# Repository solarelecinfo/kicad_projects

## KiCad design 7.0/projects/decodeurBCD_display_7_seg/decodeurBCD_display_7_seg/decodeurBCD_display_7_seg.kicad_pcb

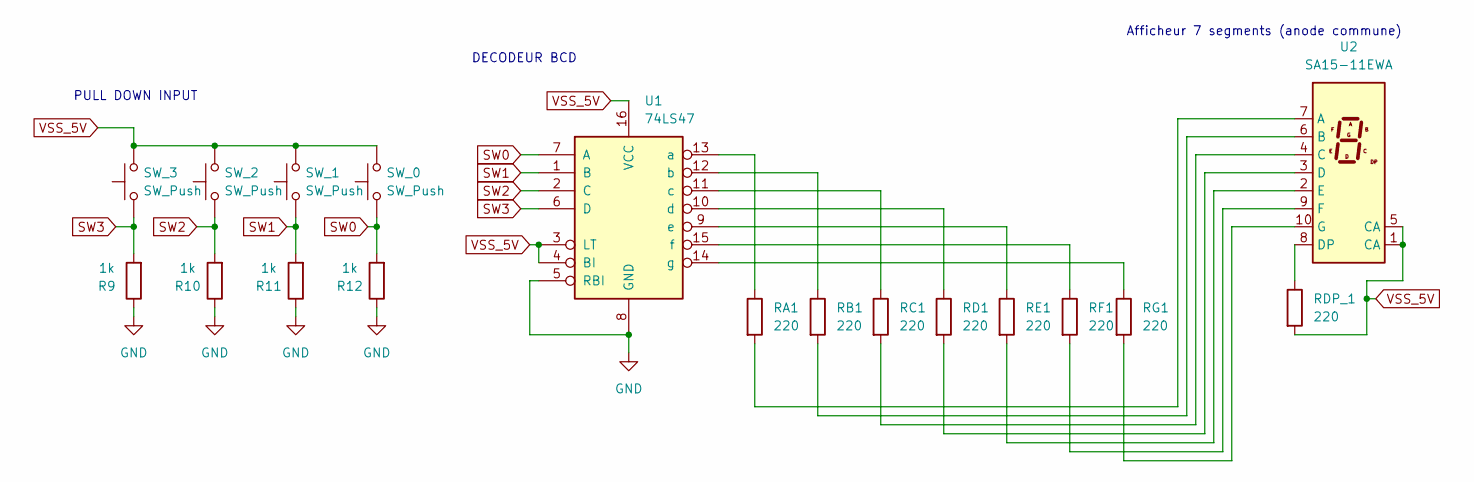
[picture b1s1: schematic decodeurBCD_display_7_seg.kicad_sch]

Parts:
R9, R10, R11, R12: 1k; R_Axial_DIN0411_L9.9mm_D3.6mm_P7.62mm_Vertical
RA1: 220; R_Axial_DIN0411_L9.9mm_D3.6mm_P7.62mm_Vertical
RB1: 220; R_Axial_DIN0411_L9.9mm_D3.6mm_P7.62mm_Vertical
RC1: 220; R_Axial_DIN0411_L9.9mm_D3.6mm_P7.62mm_Vertical
RD1: 220; R_Axial_DIN0411_L9.9mm_D3.6mm_P7.62mm_Vertical
RDP_1: 220; R_Axial_DIN0411_L9.9mm_D3.6mm_P7.62mm_Vertical
RE1: 220; R_Axial_DIN0411_L9.9mm_D3.6mm_P7.62mm_Vertical
RF1: 220; R_Axial_DIN0411_L9.9mm_D3.6mm_P7.62mm_Vertical
RG1: 220; R_Axial_DIN0411_L9.9mm_D3.6mm_P7.62mm_Vertical
SW_0, SW_1, SW_2, SW_3: SW_Push; SW_PUSH_6mm_H5mm
U1: 74LS47; CERDIP-16_W7.62mm_SideBrazed_Socket
U2: SA15-11EWA; SA15-11xxx

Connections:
GND: R9.1, R10.1, R11.1, R12.1, U1.5 (RBI), U1.8 (GND)
unnamed: RA1.1, U1.13 (a)
unnamed: RB1.1, U1.12 (b)
unnamed: RC1.1, U1.11 (c)
unnamed: RD1.1, U1.10 (d)
unnamed: RE1.1, U1.9 (e)
unnamed: RF1.1, U1.15 (f)
unnamed: RG1.1, U1.14 (g)
unnamed: RA1.2, U2.7 (A)
unnamed: RB1.2, U2.6 (B)
unnamed: RC1.2, U2.4 (C)
unnamed: RD1.2, U2.3 (D)
unnamed: RDP_1.1, U2.8 (DP)
unnamed: RE1.2, U2.2 (E)
unnamed: RF1.2, U2.9 (F)
unnamed: RG1.2, U2.10 (G)
SW0: R12.2, SW_0.1, U1.7 (A)
SW1: R11.2, SW_1.1, U1.1 (B)
SW2: R10.2, SW_2.1, U1.2 (C)
SW3: R9.2, SW_3.1, U1.6 (D)
VSS_5V: RDP_1.2, SW_0.2, SW_1.2, SW_2.2, SW_3.2, U1.3 (LT), U1.4 (BI), U1.16 (VCC), U2.1 (CA), U2.5 (CA)

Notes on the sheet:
PULL DOWN INPUT
DECODEUR BCD
Afficheur 7 segments (anode commune)

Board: 2 copper layers, 18 parts (0 on the bottom side), 21 nets, no tracks yet.

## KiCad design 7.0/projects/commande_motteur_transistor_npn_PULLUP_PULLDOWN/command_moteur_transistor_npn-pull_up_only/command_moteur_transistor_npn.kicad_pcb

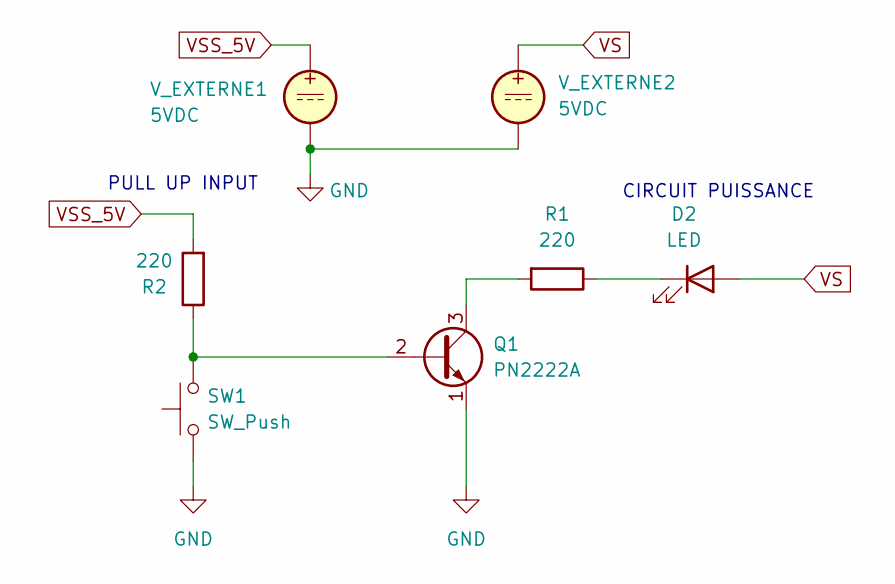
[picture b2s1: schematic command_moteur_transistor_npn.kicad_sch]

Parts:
D2: LED; LED_D5.0mm
Q1: PN2222A; TO-92_Inline
R1, R2: 220; R_Axial_DIN0411_L9.9mm_D3.6mm_P7.62mm_Vertical
SW1: SW_Push; PinSocket_1x02_P2.54mm_Vertical
V_EXTERNE1, V_EXTERNE2: 5VDC; PinHeader_1x02_P2.54mm_Horizontal

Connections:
GND: Q1.1 (E), SW1.1, V_EXTERNE1.2, V_EXTERNE2.2
unnamed: D2.1 (K), R1.1
unnamed: Q1.2 (B), R2.1, SW1.2
unnamed: Q1.3 (C), R1.2
VS: D2.2 (A), V_EXTERNE2.1
VSS_5V: R2.2, V_EXTERNE1.1

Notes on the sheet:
PULL UP INPUT
CIRCUIT PUISSANCE

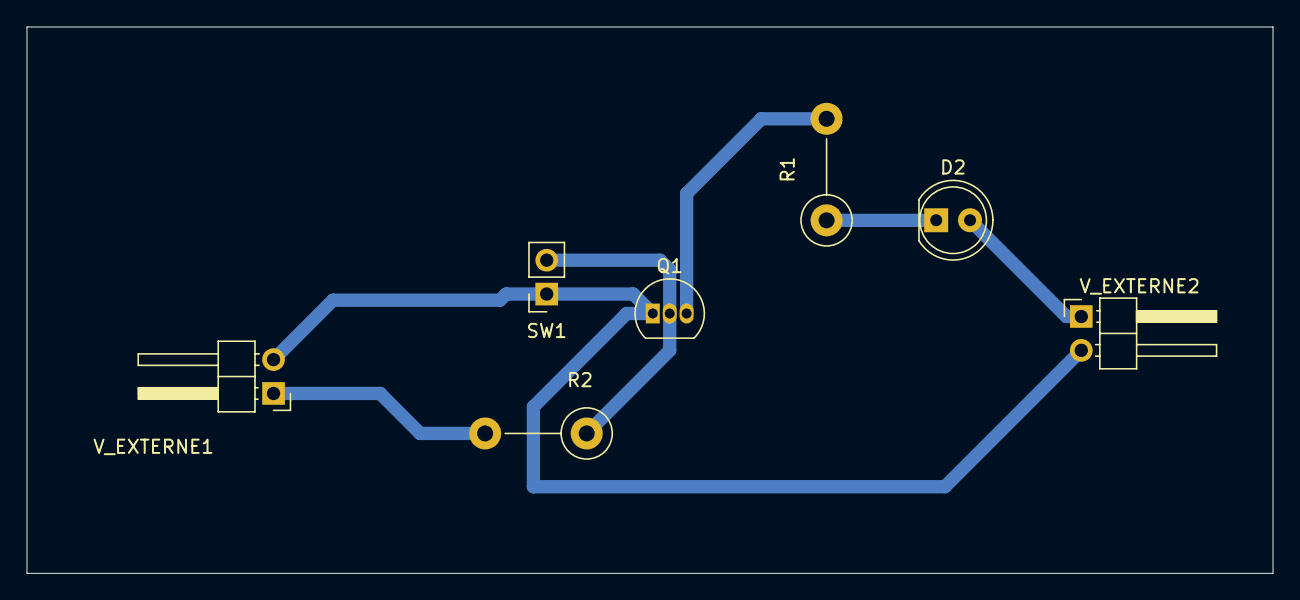
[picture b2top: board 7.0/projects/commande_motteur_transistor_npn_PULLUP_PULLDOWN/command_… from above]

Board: 2 copper layers, 93.5 x 41.0 mm, 7 parts (0 on the bottom side), 6 nets.

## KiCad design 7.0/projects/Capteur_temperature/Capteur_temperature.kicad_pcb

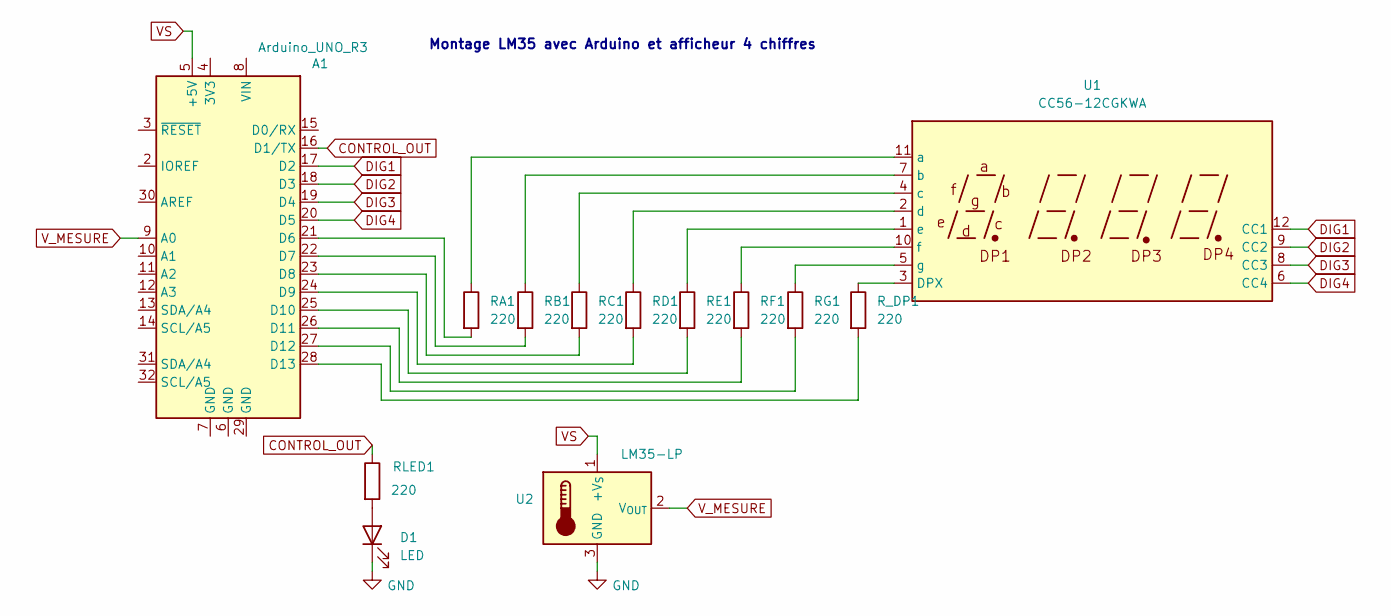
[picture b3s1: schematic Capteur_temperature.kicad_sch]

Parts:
A1: Arduino_UNO_R3
D1: LED; LED_D5.0mm
RA1: 220; R_Axial_DIN0411_L9.9mm_D3.6mm_P12.70mm_Horizontal
RB1: 220; R_Axial_DIN0411_L9.9mm_D3.6mm_P12.70mm_Horizontal
RC1: 220; R_Axial_DIN0411_L9.9mm_D3.6mm_P12.70mm_Horizontal
RD1: 220; R_Axial_DIN0411_L9.9mm_D3.6mm_P12.70mm_Horizontal
RE1: 220; R_Axial_DIN0411_L9.9mm_D3.6mm_P12.70mm_Horizontal
RF1: 220; R_Axial_DIN0411_L9.9mm_D3.6mm_P12.70mm_Horizontal
RG1: 220; R_Axial_DIN0411_L9.9mm_D3.6mm_P12.70mm_Horizontal
RLED1: 220; R_Axial_DIN0411_L9.9mm_D3.6mm_P12.70mm_Horizontal
R_DP1: 220; R_Axial_DIN0411_L9.9mm_D3.6mm_P12.70mm_Horizontal
U1: CC56-12CGKWA; CA56-12CGKWA
U2: LM35-LP; TO-92_Inline

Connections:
CONTROL_OUT: A1.16 (D1/TX), RLED1.1
DIG1: A1.17 (D2), U1.12 (CC1)
DIG2: A1.18 (D3), U1.9 (CC2)
DIG3: A1.19 (D4), U1.8 (CC3)
DIG4: A1.20 (D5), U1.6 (CC4)
GND: D1.1 (K), U2.3 (GND)
unnamed: A1.21 (D6), RA1.2
unnamed: A1.22 (D7), RB1.2
unnamed: A1.23 (D8), RC1.2
unnamed: A1.24 (D9), RD1.2
unnamed: A1.25 (D10), RE1.2
unnamed: A1.26 (D11), RF1.2
unnamed: A1.27 (D12), RG1.2
unnamed: A1.28 (D13), R_DP1.2
unnamed: D1.2 (A), RLED1.2
unnamed: R_DP1.1, U1.3 (DPX)
unnamed: RA1.1, U1.11 (a)
unnamed: RB1.1, U1.7 (b)
unnamed: RC1.1, U1.4 (c)
unnamed: RD1.1, U1.2 (d)
unnamed: RE1.1, U1.1 (e)
unnamed: RF1.1, U1.10 (f)
unnamed: RG1.1, U1.5 (g)
VS: A1.5 (+5V), U2.1 (+V_{S})
V_MESURE: A1.9 (A0), U2.2 (V_{OUT})

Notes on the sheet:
Montage LM35 avec Arduino et afficheur 4 chiffres

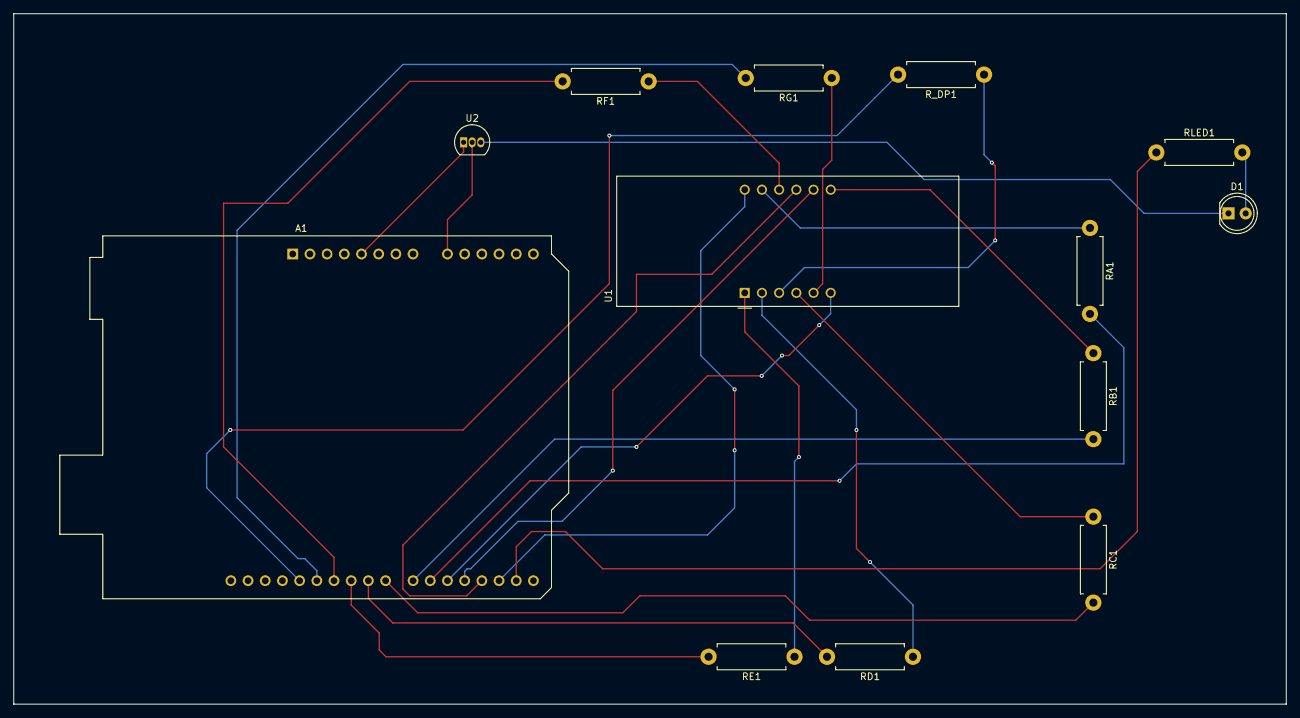
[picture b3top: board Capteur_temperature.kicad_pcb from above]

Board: 2 copper layers, 188.0 x 102.0 mm, 13 parts (0 on the bottom side), 25 nets.

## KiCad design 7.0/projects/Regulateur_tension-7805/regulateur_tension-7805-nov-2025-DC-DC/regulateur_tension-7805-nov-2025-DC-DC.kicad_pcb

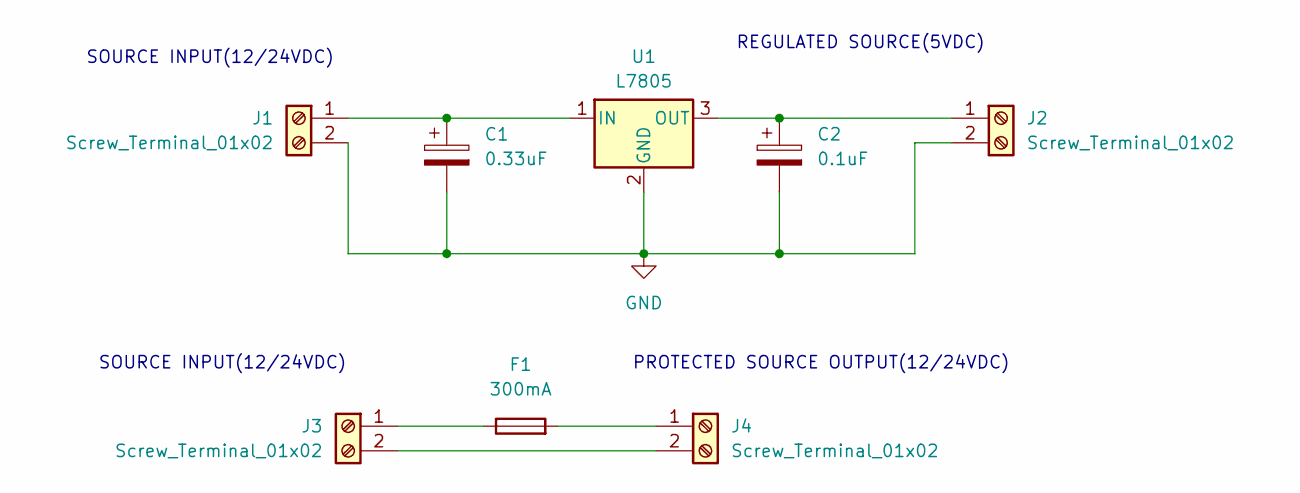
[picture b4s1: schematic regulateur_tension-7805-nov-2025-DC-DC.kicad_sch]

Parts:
C1: 0.33uF; C_Rect_L7.0mm_W4.5mm_P5.00mm
C2: 0.1uF; C_Rect_L7.0mm_W4.5mm_P5.00mm
F1: 300mA; Fuseholder_Cylinder-5x20mm_Stelvio-Kontek_PTF78_Horizontal_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
J1, J2, J3, J4: Screw_Terminal_01x02; PinHeader_1x02_P2.54mm_Vertical
U1: L7805; TO-220-3_Vertical

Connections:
GND: C1.2, C2.2, J1.2, J2.2, U1.2 (GND)
unnamed: C1.1, J1.1, U1.1 (IN)
unnamed: C2.1, J2.1, U1.3 (OUT)
unnamed: F1.1, J3.1
unnamed: J3.2, J4.2
unnamed: F1.2, J4.1

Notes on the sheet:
SOURCE INPUT(12/24VDC)
PROTECTED SOURCE OUTPUT(12/24VDC)
REGULATED SOURCE(5VDC)

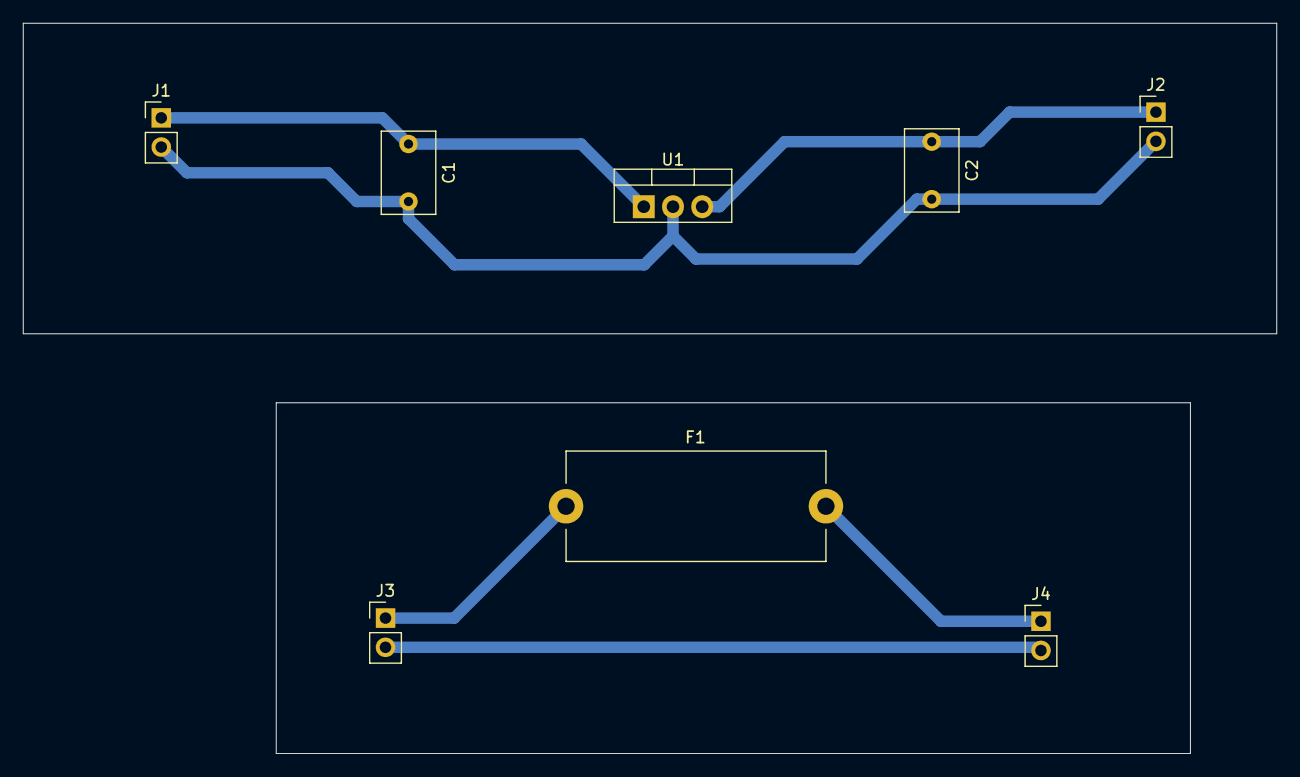
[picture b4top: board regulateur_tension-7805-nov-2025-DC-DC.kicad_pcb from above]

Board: 2 copper layers, 109.0 x 63.5 mm, 8 parts (0 on the bottom side), 6 nets.

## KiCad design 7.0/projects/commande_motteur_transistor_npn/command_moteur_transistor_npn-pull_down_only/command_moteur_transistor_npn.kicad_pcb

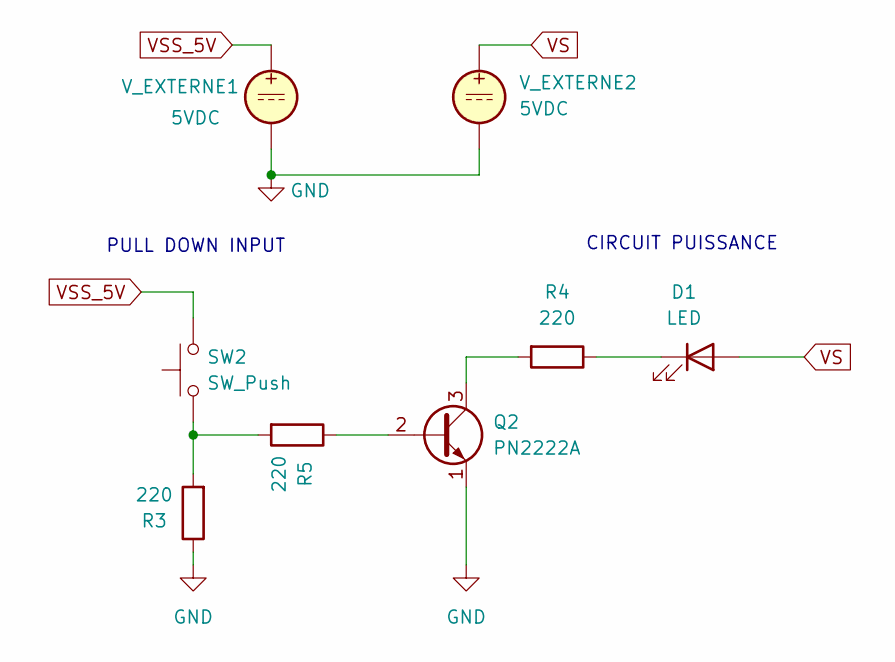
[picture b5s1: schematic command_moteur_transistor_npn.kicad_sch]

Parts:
D1: LED; LED_D5.0mm
Q2: PN2222A; TO-92_Inline
R3, R4, R5: 220; R_Axial_DIN0411_L9.9mm_D3.6mm_P7.62mm_Vertical
SW2: SW_Push; PinSocket_1x02_P2.54mm_Vertical
V_EXTERNE1, V_EXTERNE2: 5VDC; PinHeader_1x02_P2.54mm_Horizontal

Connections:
GND: Q2.1 (E), R3.1, V_EXTERNE1.2, V_EXTERNE2.2
unnamed: D1.1 (K), R4.1
unnamed: Q2.2 (B), R5.1
unnamed: Q2.3 (C), R4.2
unnamed: R3.2, R5.2, SW2.1
VS: D1.2 (A), V_EXTERNE2.1
VSS_5V: SW2.2, V_EXTERNE1.1

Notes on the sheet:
CIRCUIT PUISSANCE
PULL DOWN INPUT

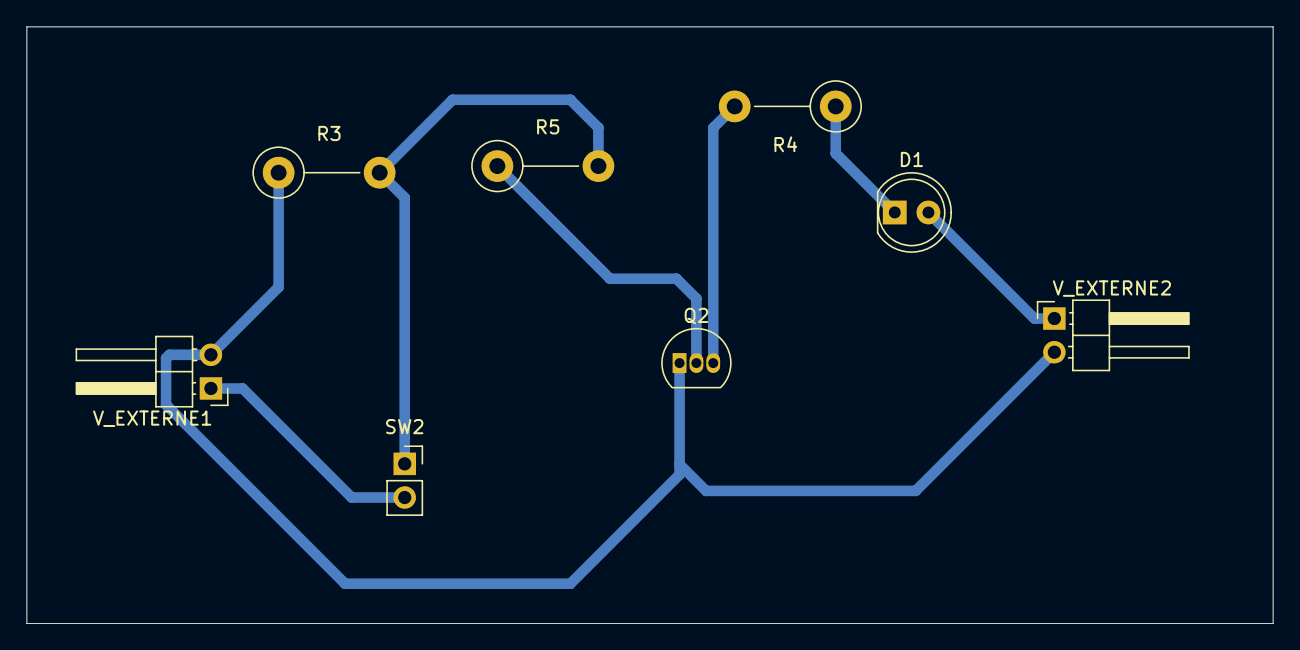
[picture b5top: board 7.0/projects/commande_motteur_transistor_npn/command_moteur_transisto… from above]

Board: 2 copper layers, 94.0 x 45.0 mm, 8 parts (0 on the bottom side), 7 nets.

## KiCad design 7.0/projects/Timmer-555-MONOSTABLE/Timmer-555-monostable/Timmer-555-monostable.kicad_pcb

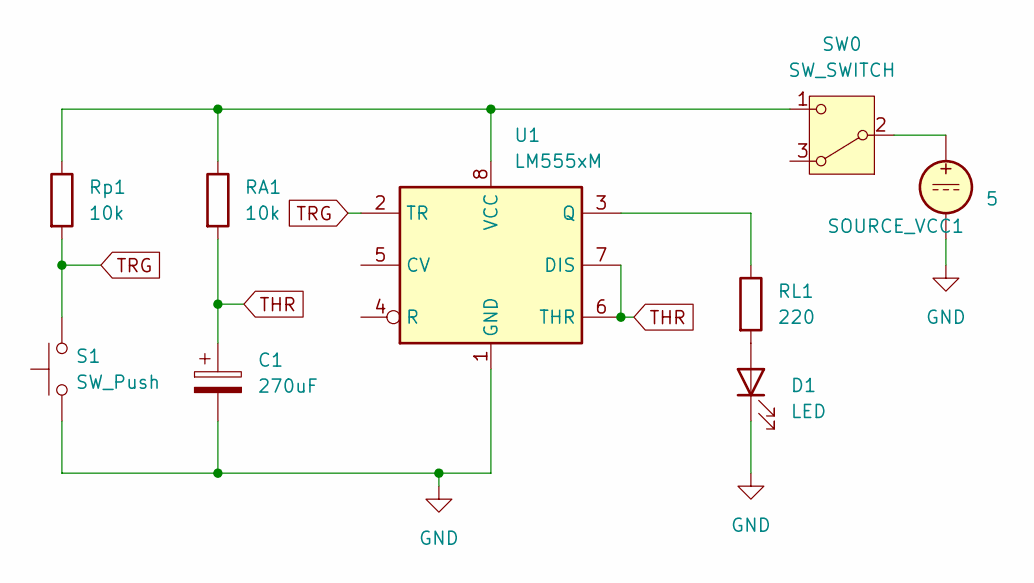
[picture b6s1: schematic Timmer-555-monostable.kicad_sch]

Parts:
C1: 270uF; CP_Radial_D10.0mm_P7.50mm
D1: LED; LED_D5.0mm
RA1: 10k; R_Axial_DIN0207_L6.3mm_D2.5mm_P7.62mm_Horizontal
RL1: 220; R_Axial_DIN0207_L6.3mm_D2.5mm_P7.62mm_Horizontal
Rp1: 10k; R_Axial_DIN0207_L6.3mm_D2.5mm_P7.62mm_Horizontal
S1: SW_Push; SW_PUSH_6mm_H5mm
SOURCE_VCC1: 5; AMASS_XT30U-M_1x02_P5.0mm_Vertical
SW0: SW_SWITCH; TerminalBlock_MaiXu_MX126-5.0-03P_1x03_P5.00mm
U1: LM555xM; DIP-8_W7.62mm_Socket_LongPads

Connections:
GND: C1.2, D1.1 (K), S1.1, SOURCE_VCC1.2, U1.1 (GND)
unnamed: D1.2 (A), RL1.2
unnamed: SOURCE_VCC1.1, SW0.2 (B)
unnamed: RA1.1, Rp1.1, SW0.1 (C), U1.8 (VCC)
unnamed: RL1.1, U1.3 (Q)
THR: C1.1, RA1.2, U1.6 (THR), U1.7 (DIS)
TRG: Rp1.2, S1.2, U1.2 (TR)

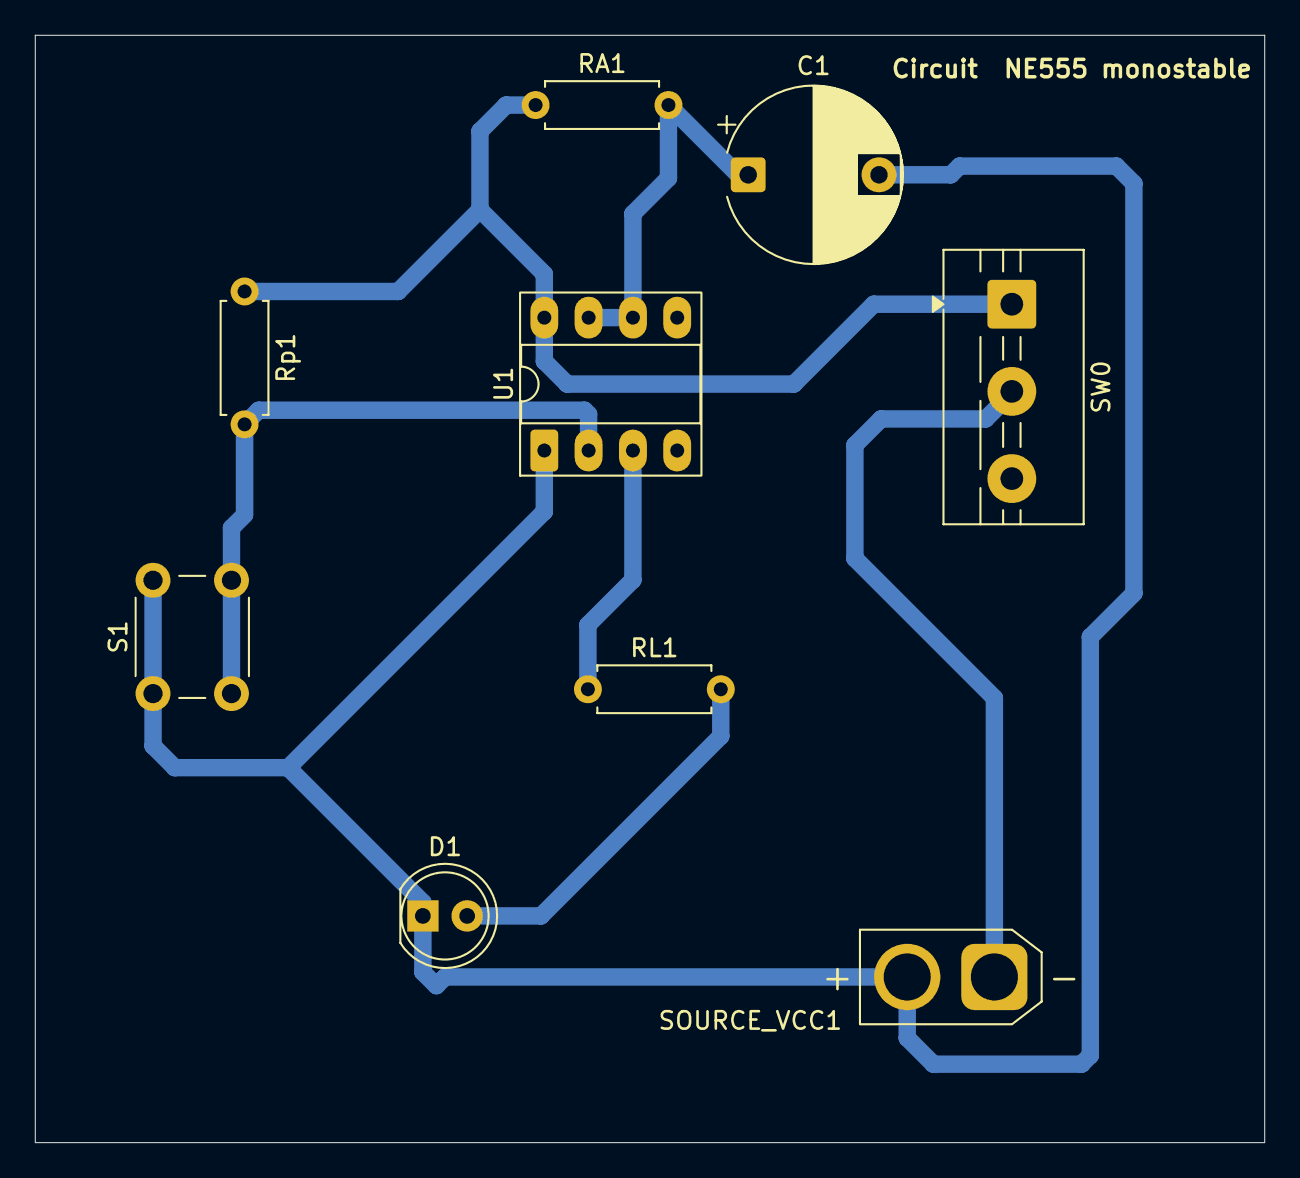
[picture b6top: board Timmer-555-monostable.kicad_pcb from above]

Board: 2 copper layers, 70.5 x 63.5 mm, 9 parts (0 on the bottom side), 7 nets.

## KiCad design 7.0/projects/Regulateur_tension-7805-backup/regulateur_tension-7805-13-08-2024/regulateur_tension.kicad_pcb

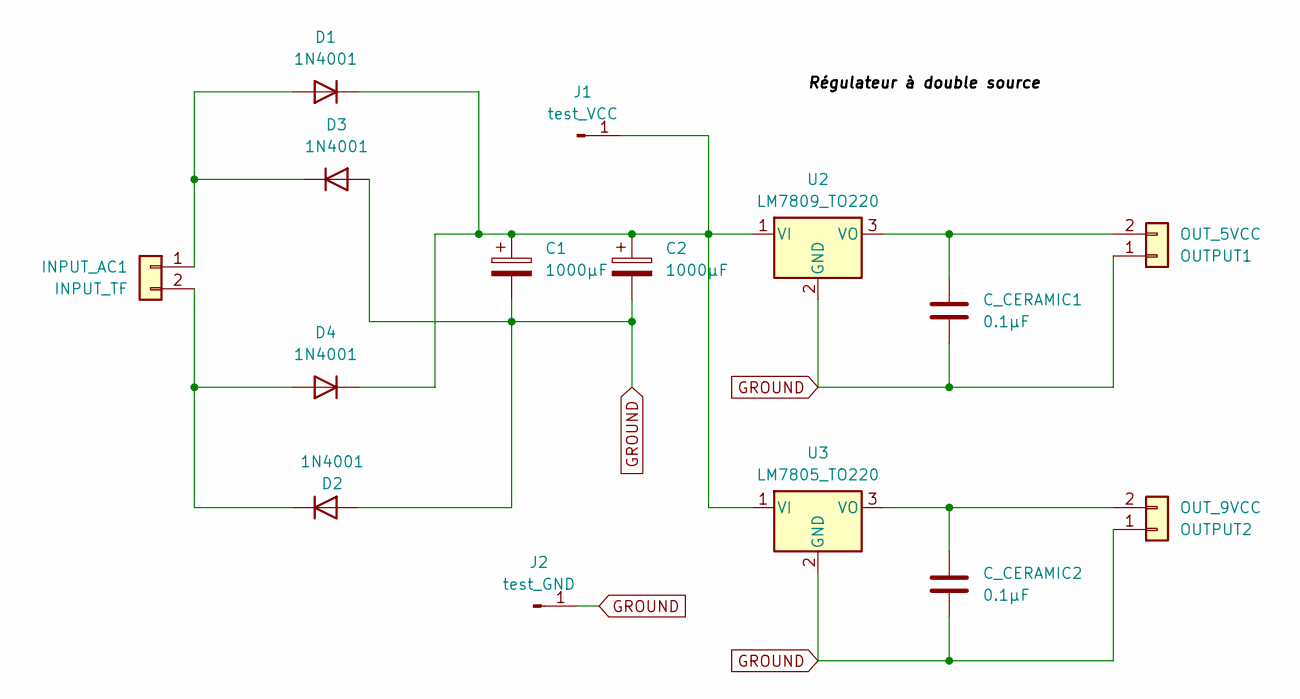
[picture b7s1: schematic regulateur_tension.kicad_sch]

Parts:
C1, C2: 1000μF; CP_Radial_D13.0mm_P7.50mm
C_CERAMIC1, C_CERAMIC2: 0.1μF; C_Disc_D7.5mm_W2.5mm_P5.00mm
D1, D2, D3, D4: 1N4001; D_DO-41_SOD81_P10.16mm_Horizontal
INPUT_AC1: INPUT_TF; TerminalBlock_MetzConnect_Type094_RT03502HBLU_1x02_P5.00mm_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
J1: test_VCC; PinHeader_1x01_P2.54mm_Vertical
J2: test_GND; PinHeader_1x01_P2.54mm_Vertical
OUTPUT1: OUT_5VCC; TerminalBlock_MetzConnect_Type094_RT03502HBLU_1x02_P5.00mm_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
OUTPUT2: OUT_9VCC; TerminalBlock_MetzConnect_Type094_RT03502HBLU_1x02_P5.00mm_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
U2: LM7809_TO220; TO-220-3_Vertical
U3: LM7805_TO220; TO-220-3_Vertical

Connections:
GROUND: C1.2, C2.2, C_CERAMIC1.2, C_CERAMIC2.2, D2.2 (A), D3.2 (A), J2.1, OUTPUT1.1, OUTPUT2.1, U2.2 (GND), U3.2 (GND)
unnamed: D1.2 (A), D3.1 (K), INPUT_AC1.1
unnamed: C1.1, C2.1, D1.1 (K), D4.1 (K), J1.1, U2.1 (VI), U3.1 (VI)
unnamed: D2.1 (K), D4.2 (A), INPUT_AC1.2
unnamed: C_CERAMIC1.1, OUTPUT1.2, U2.3 (VO)
unnamed: C_CERAMIC2.1, OUTPUT2.2, U3.3 (VO)

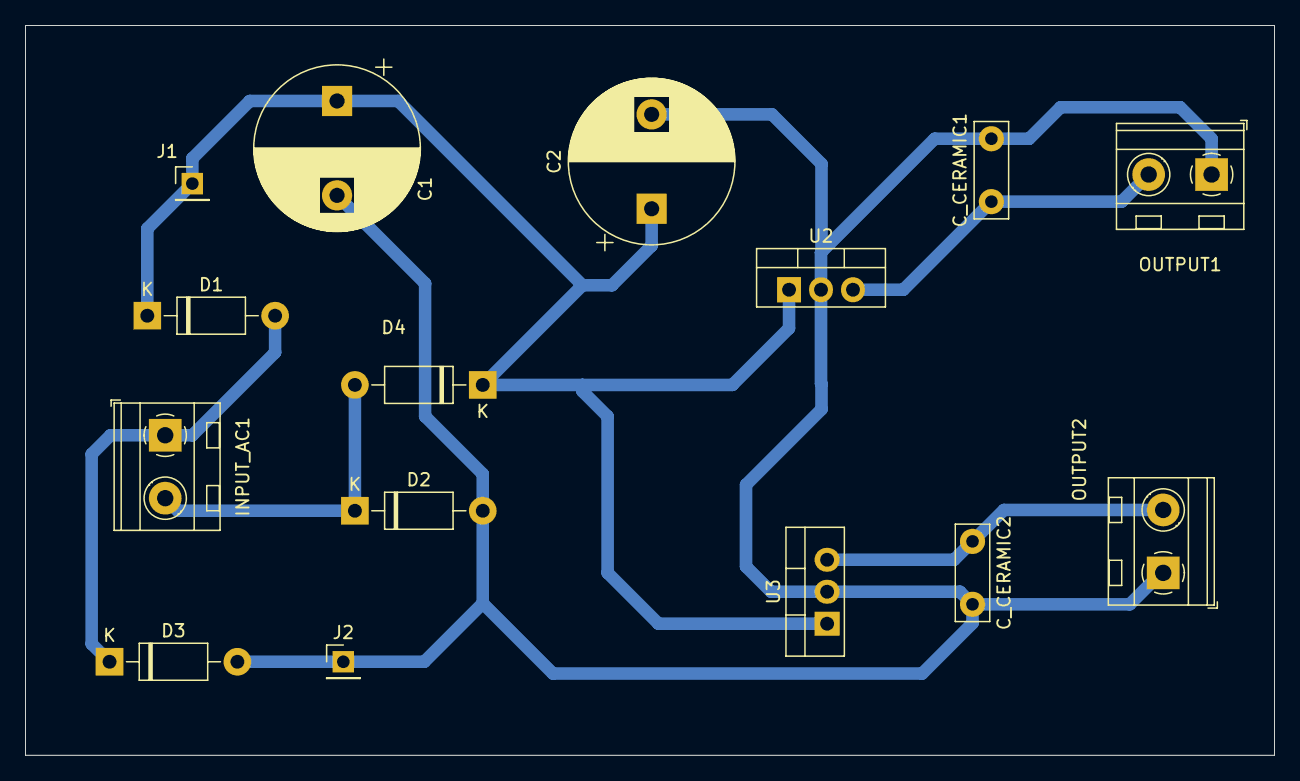
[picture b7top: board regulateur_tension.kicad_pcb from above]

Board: 2 copper layers, 99.3 x 58.0 mm, 15 parts (0 on the bottom side), 6 nets.

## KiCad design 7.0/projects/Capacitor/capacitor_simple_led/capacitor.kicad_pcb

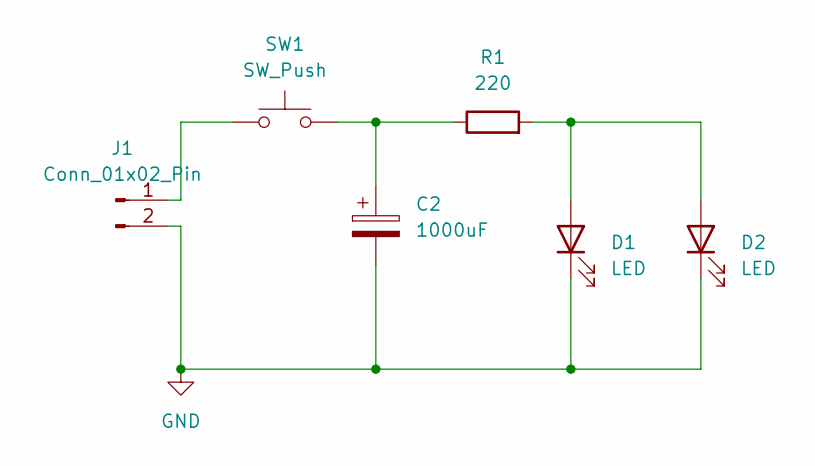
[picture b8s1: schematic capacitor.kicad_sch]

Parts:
C2: 1000uF; CP_Radial_D13.0mm_P7.50mm
D1, D2: LED; LED_D5.0mm
J1: Conn_01x02_Pin; TerminalBlock_MetzConnect_Type094_RT03502HBLU_1x02_P5.00mm_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
R1: 220; R_Axial_DIN0414_L11.9mm_D4.5mm_P15.24mm_Horizontal
SW1: SW_Push; SW_PUSH_6mm_H7.3mm

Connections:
GND: C2.2, D1.1 (K), D2.1 (K), J1.2
unnamed: C2.1, R1.1, SW1.2
unnamed: D1.2 (A), D2.2 (A), R1.2
unnamed: J1.1, SW1.1

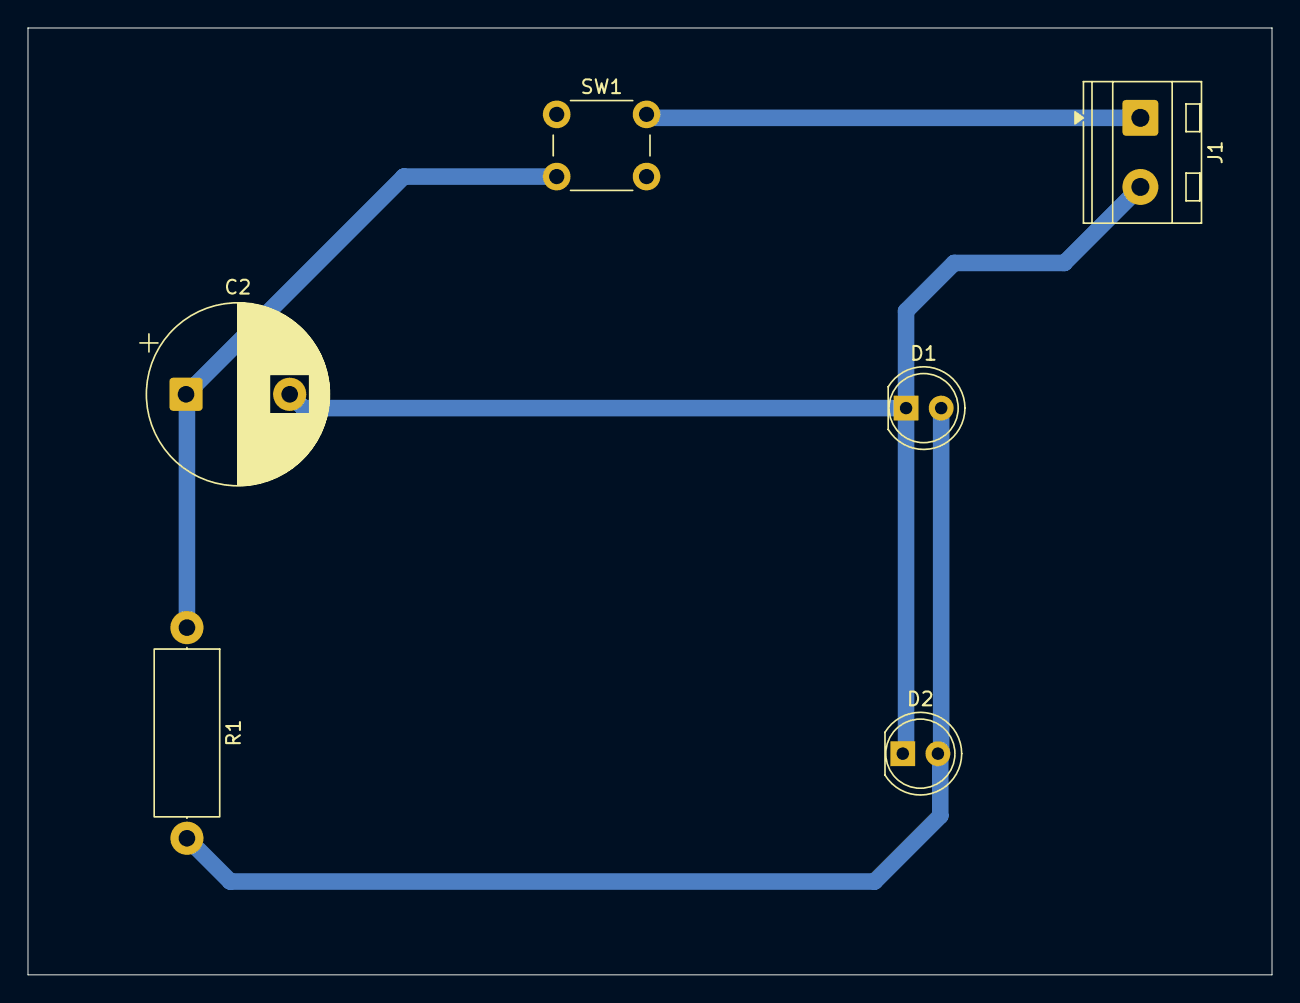
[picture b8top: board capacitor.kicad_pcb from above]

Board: 2 copper layers, 90.0 x 68.5 mm, 6 parts (0 on the bottom side), 4 nets.

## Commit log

2024-02-20 #first kikadcommit
2024-07-26 # This is a combination of 5 commits.
    add commit deux
    adding some extra backup for rl
    clamper AC example OK
    # This is a combination of 2 commits.
    new elements
    test2
2024-07-26 teste2
2024-10-13 addition exercie control daccess -cirucit transfo
2024-10-13 alll
2024-10-13 exercise1 test
2024-10-13 deux
2024-10-13 valid3
2024-10-13 example
2024-10-13 new modifcation
2024-10-19 checkpoint-OK-multiple-piste-trace-1.5mm
2024-10-19 checkpoint-OK-multiple-piste-trace-1.5mm-OK
2024-10-22 final-final
2025-01-26 adding timmer 55 project
2025-04-08 adding adc schemla
2025-04-09 info
2025-04-16 adding sample projects
2025-05-15 adding projects
2025-05-24 adding project for timmer 555 potentiometer
2025-06-18 adding regulateur
2025-06-26 adding example
2025-07-05 adding video BJT
2025-07-09 adding bjt transisor
2025-07-18 adding other projects
2025-08-17 adding TP for 7805 et 7809 regulator
2025-10-24 adding 555 example
2025-10-24 adding 555 monostable
2025-10-25 adding lm7805 circuit
2025-10-26 adding 555-monostable ok
2025-10-29 all info
2025-10-29 adding goog values for 555 project
2025-10-29 adding timmer 555
2025-11-08 kicad info
2025-11-26 adding somme kicad corrections
2025-11-26 adding info of files
2025-12-02 info vcc
2025-12-03 adding npn
2025-12-08 adding all circuits
2025-12-08 adding fuses
2025-12-19 connecteur jack
2025-12-27 info info
2025-12-27 adding capteur temperrature OK
2025-12-31 adding info
2026-01-01 adding 7 segment display
